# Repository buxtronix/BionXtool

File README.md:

# BionXtool

**BionXtool** is a tool for diagnostics, configuration, and real-time monitoring of BionX e-bike
components (Console, Battery, and Motor). Together with a cheap ($10) USB-CAN interface,
it can replace almost all of the functionality of the official BBI Software and hardware
interface ($100).

It is a fork of the original [BigXionFlasher](https://bigxionflasher.org) project,
with the following enhancements:

- Uses a cheap off the shelf USB Canbus adapter and standard Linux CAN networking
- Read and write any bike registers
- Real-time sniffing of the CANbus for diagnostics and more
- Sniff from PCAP files for offline analysis

I write this fork as I had dusted off my old mothballed BionX system, and needed to adjust some
limits to comply with updated legislation in my jurisdiction. With the company defunct, I couldn't
get a dealer to reset it, and wanted to use a cheap Aliexpress CAN adapter.

> [!WARNING]
> A non-compliant system must not be ridden in public spaces, any limits changed with this tool
> must be compliant with local regulations. As well as legal trouble, raising speed limits can
> put yourself, others, and your bike in danger.

> [!WARNING]
> Setting certain registers may leave your system unusable or difficult to recover. Please take
> extra care when manually setting registers.

---

## 🚀 Key Features

- **System Diagnostics**: View detailed hardware/software versions, serial numbers, and health statistics (cycle counts, temperature, voltage).
- **Configuration**: Modify speed limits (Assist, Throttle, and Min Speed), console preferences, accessory voltage and more
- **Advanced Sniffing**: Real-time or file-based (PCAP) CAN-bus monitoring with automatic register decoding into human-readable names and values.
- **Direct Register Access**: Read and write any specific BionX register from any node using hex IDs or friendly names.

For a detailed description of the BionX CANBus protocol, see [PROTOCOL.md](PROTOCOL.md)..

---

## 🛠 Installation

### Hardware prerequisites
- A BionX e-bike system using the CANBus protocol (post 2009 with G1/G2 console)
- A USB CANBus interface running Candlelight (e.g CANable 2.0)
- A way to physically connect to the bike CANBus (see below).

### Software Prerequisites
- A Linux system with **SocketCAN** support.
- `gcc` and `make` build tools.
- `libncurses` for monitor mode.

### Building from Source
```bash
git clone https://github.com/buxtronix/BionXtool.git
cd BionXtool
make
```

---

## 🔌 Hardware Setup

There are a few ways to interface with the CANBus on the bike. For reference,
see this [wiring diagram](images/pinout.png).

### Connect to the existing plugs

The official way to connect (which is what the dealer interface does) is to
use a tap cable inline where the console connector plug is. To do this, you
need a pair of Hirose connectors (HR30-6J-6P and HR30-6P-6S), wire all 6 pins
up in a straight through configuration, and tap off the GND, CAN_L and CAN_H
connections into the CANBus adapter.

The connectors are however fairly expensive (about $20/pair).

### Tap off the battery connector.

The cheapest way is to tap lines off the battery connector by just soldering
wires to them.

To access this, you need to remove the battery bracket off the bike, unscrew
the two Torx screws underneath, remove the metal bracket and you will get
access to the back of the plug. You may need to remove some hot glue first.
Then you just solder wires to tap off pins 2 (CAN_H), 5 (CAN_L) and GND. You
need to take care not to short or unsolder the wrong wires as there are
high currents and moderate voltages (50v) present.

### Console shim

I have developed a slim flex PCB that slides under the console where
it taps off the pogo pins. This is quite cheap, about $5 delivered from
JLCPCB, then once mounted you solder wires to the flex PCB that sticks out
from under the console.

For details, see [here](adapter-pcb/).

## 🔌 Software Setup

Most CANable adapters come from the factory with _slcan_ firmware, so you
will need to flash the _candlelight_ firmware onto it instead. This is really
simple, you just plug it into a computer and click a couple of buttons on
the [updater page](https://canable.io/updater/canable2.html).

BionX systems communicate at a bitrate of **125,000 bits/s**. Before running the
tool, you must bring up your CAN interface with the correct settings.

```bash
# Bring up can0 with the BionX bitrate (125k)
sudo ip link set can0 type can bitrate 125000
sudo ip link set can0 up
```

If you are testing without hardware, you can use a virtual CAN interface:
```bash
sudo modprobe vcan
sudo ip link add dev vcan0 type vcan
sudo ip link set vcan0 up
./BionXtool -d vcan0 -S
```
---

## 📖 Usage

BionXtool provides several modes of operation, from high-level configuration to low-level protocol analysis.

### 1. System Overview & Diagnostics
Retrieve a comprehensive report of all connected components, including software versions, battery health, and odometer.

```bash
# Print all system settings and statistics
$ ./BionXtool -s
BionXtool V 0.1 (BionXtool)
 (c) 2026 by Ben Buxton <bbuxton@gmail.com>

console already in slave mode. good!

Console information:
 hardware version ........: 0x15
 software version ........: 0x64
 manufacture date ........: 13/01/2014
 assistance level ........: 3 (0x03)
 part number .............: 03205
 item number .............: 00342
 max limit enabled .......: yes
 speed limit .............: 26.0 km/h
 min limit enabled .......: yes
 min speed limit .........: 0.2 km/h
 throttle limit enabled ..: yes
 throttle speed limit ....: 6.0 km/h
 wheel circumference .....: 2075
 mountain cap ............: 54.69%
 odo .....................: 14258.40 km

Battery information:
 hardware version ........: 0x63
 software version ........: 0x112
 manufacture date ........: 07/09/2017
 part number .............: 05560
 item number .............: 00342
 voltage .................: 53.13 V
 battery level ...........: 100.00%
 maximum voltage .........: 112.08%
 minimum voltage .........: 95.42%
 mean voltage ............: 110.00%
 resets ..................: 0
 lmd .....................: 10.40 Ah
 cell capacity ...........: 2.15 Ah
 charge time worst .......: 113
 charge time mean ........: 0
 charge cycles ...........: 268
 full charge cycles ......: 0
 power cycles ............: 969
 battery temp max ........: 80°C
 battery temp min ........: -17°C
 accessory voltage config.: 8.20 V
 RTC timestamp............: 2088d 16:40:16

 charge level @ 010% : 0015
 charge level @ 020% : 0015
 charge level @ 030% : 0072
 charge level @ 040% : 0088
 charge level @ 050% : 0023
 charge level @ 060% : 0028
 charge level @ 070% : 0020
 charge level @ 080% : 0004
 charge level @ 090% : 0003
 charge level @ 100% : 0003
 total # of charges .: 0271

 balancer enabled ...: no

 voltage cell #01 ...: 4.085V
 voltage cell #02 ...: 4.083V
 voltage cell #03 ...: 4.080V
 voltage cell #04 ...: 4.086V
 voltage cell #05 ...: 4.081V
 voltage cell #06 ...: 4.088V
 voltage cell #07 ...: 4.086V
 voltage cell #08 ...: 4.091V
 voltage cell #09 ...: 4.098V
 voltage cell #10 ...: 4.083V
 voltage cell #11 ...: 4.066V
 voltage cell #12 ...: 4.114V
 voltage cell #13 ...: 4.088V
 temperature pack #01: 29°C
 temperature pack #02: 29°C
 temperature pack #03: 29°C
 temperature pack #04: 29°C
 temperature pack #05: 14°C

Motor information:
 hardware version ........: 0x32
 software version ........: 0x102
 manufacture date ........: 09/11/2017
 temperature .............: 37°C
 speed limit .............: 26 km/h
 wheel circumference .....: 2075
 part number .............: 05989
 item number .............: 00342

```

### 2. Configuring System Limits & Geometry
Adjust the behavior of the bike to match local regulations or your preferences.

```bash
# Set assist speed limit to 32.0 km/h (0 for unlimited)
./BionXtool -l 32.0

# Set throttle speed limit to 20.0 km/h
./BionXtool -t 20.0

# Set minimum assist speed (speed at which motor kicks in)
./BionXtool -m 2.0

# Update wheel circumference (in mm) for accurate speed/distance
./BionXtool -c 2073

# Set initial assist level on power-up (0-4)
./BionXtool -a 2

# Set mountain cap level (assist percentage)
./BionXtool -o 55

# Set clock to current local time
./BionXtool -T
```

### 3. Battery & Accessory Configuration
Configure battery-specific settings like accessory port voltage.

```bash
# Set accessory port voltage (6.0V to 14.0V)
./BionXtool -v 12.0

# Enable/Disable accessory power (1=On, 0=Off)
./BionXtool -A 1
```

### 4. CAN Bus Monitoring & Sniffing
Analyze the live communication between the console, battery, and motor.

```bash
# Real-time TUI dashboard (Top-like interface)
./BionXtool -M

# Stream every CAN packet with human-readable decoding
./BionXtool -S

# Stream only when a register value changes
./BionXtool -C

# Analyze a previously captured PCAP file
./BionXtool -f capture.pcap
```

Included in this repo are two captures. `bike-on-off.pcap` is a raw PCAP sniff
from my bike being turned on, then turned off shortly after. `bike-on-off-txt`
is the same but decoded.

### 5. Direct Register Access (Expert)
Read or write individual registers on any node. Useful for advanced features or deep troubleshooting.

```bash
# Read Battery Hardware Revision (0x3B)
./BionXtool -R battery 0x3B

# Set config to enable accessory power at bike turn-on.
./BionXtool -W console 0x80 0x1
```

An almost complete list of all registers is in [registers.h](registers.h). Note
that interacting with the console requires first setting it into slave mode (-z),
however this is not required for other components.

### 6. Power & State Control
Force system states or perform remote operations.

```bash
# Power off the entire system
./BionXtool -p

# Force console into slave mode (for external control)
./BionXtool -z

# Run commands without attempting to trigger slave mode
./BionXtool -n -S
```

---

## 📋 Command Line Options

| Option | Argument | Description |
| :--- | :--- | :--- |
| **Global** | | |
| `-d` | `<device>` | CAN device interface (default: `can0`) |
| `-h` | | Print help screen |
| **Information** | | |
| `-s` | | Print system settings overview |
| `-i` | | Hide private serial and part numbers |
| **Configuration** | | |
| `-l` | `<speed>` | Set assist speed limit (0-70 km/h, 0=unlimited) |
| `-t` | `<speed>` | Set throttle speed limit (0-70 km/h) |
| `-m` | `<speed>` | Set minimum assist speed (0-30 km/h) |
| `-c` | `<mm>` | Set wheel circumference (in mm) |
| `-a` | `<level>` | Set initial assist level (0-4) |
| `-o` | `<pct>` | Set mountain cap assist level (0-100%) |
| `-v` | `<volt>` | Set battery accessory voltage (6.0 - 14.0V) |
| `-A` | `<0\|1>` | Set battery accessory power (0=off, 1=on) |
| `-T` | | Update clock (RTC). Stored in battery |
| **Sniffing** | | |
| `-M` | | **Monitor Mode**: Interactive TUI dashboard |
| `-S` | | **Sniff Mode**: Stream decoded packets |
| `-C` | | **Change Sniff**: Stream only changed values |
| `-f` | `<file>` | Sniff from a PCAP file |
| **Low-level** | | |
| `-R` | `<node> <reg>`| Read specific register (hex) from node (name or hex) |
| `-W` | `<node> <reg> <val>`| Write value to specific register |
| `-z` | | Force console into slave mode |
| `-n` | | Do NOT attempt to trigger slave mode |
| `-p` | | Power off system |

---

## 🛠Changelog

- 2026-04-14: rtc support. various register clarifications
- 2026-03-28: added adapter pcb info
- 2026-03-06: initial version

## ⚖️ License & Attribution

**BionXtool** is licensed under the **GPLv3**.

This project is a fork of **BigXionFlasher**, originally developed by **Thomas König**. 
It includes software developed by the BigXionFlasher Project (http://www.bigxionflasher.org/).

Gemini CLI is used to assist coding tasks. Actual hardware engineering lovingly
done by hand :)

**Author of this fork:** Ben Buxton <bbuxton@gmail.com> (2026)

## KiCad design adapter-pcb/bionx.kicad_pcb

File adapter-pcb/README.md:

# Bionx Console Adapter

This contains Kicad designs for a flex PCB that can be slotted under the
G2 console for easy interfacing with the bike's CAN bus.

The PCB breaks out all of the pins from the console (including throttle).

## Manufacture

The file `gerbers.zip` contains all of the necessary fab files and it
can be uploaded directly to JLCPCB and other board houses, with no
further changes necessary.

JLCPCB currently has a deal where you can get 5 x flex PCBs for $2,
and if you use their lowest cost shipping option, you can get these
delivered for a total of around $5-6.

Five easy steps to order:

1. Go to [JLCPCB](https://jlcpcb.com/)
2. Click on the *Get Instant Quote* button (no need to change the options next to it).
3. Click *Add gerber file* and upload the _gerbers.zip_ file from here.
4. Select *Flex* as the base material. You will see a yellow render of the PCB.
5. Change no other options, just click *Save to cart* and finalise the order.

If you select *Global Standard Direct Line* shipping, this will cost a
little over $3, rather than $20+ for DHL/Fedex, though will take a couple
of weeks.

The $2 deal is for 0.11mm PCB - thicker options are much more expensive,
but this one works (you may want to manually add a stiffening film).

## Usage

The PCB simply slips into the console holder, ensuring the PCB pads line
up with the metal pads, then slide the console on, taking care not to
let the PCB slip.

On mine, I added a little extra rigidity by using some 0.2mm mylar
sheet that I cut and added holes for the PCB pads, using contact cement
to bond them together. You don't have to do this, but you need to
be a little careful at preventing the PCB from slipping.

You can then solder wires to the GND, CAN_L and CAN_H pads, which you
then connect to your CANBus adapter. I used soft silicone wire and hot
glue - more rigid wire and/or no hot glue risks tearing the pads off.

The other pins are also broken out for those who want to experiment more.

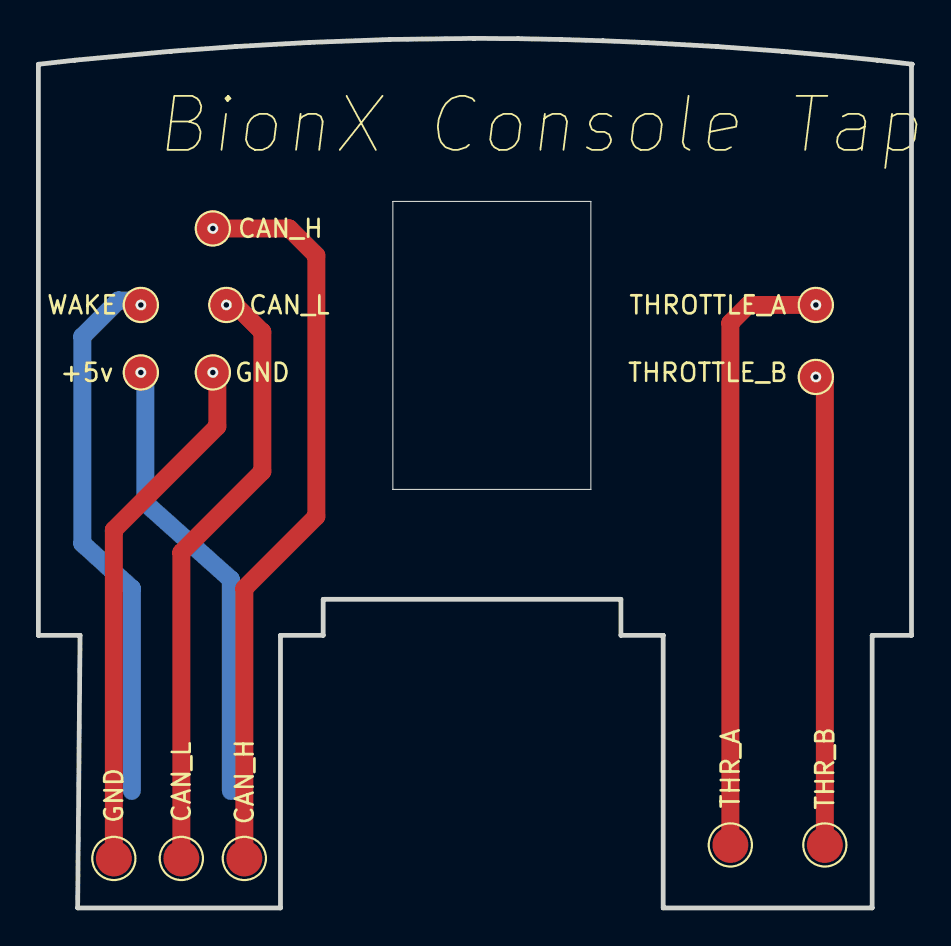
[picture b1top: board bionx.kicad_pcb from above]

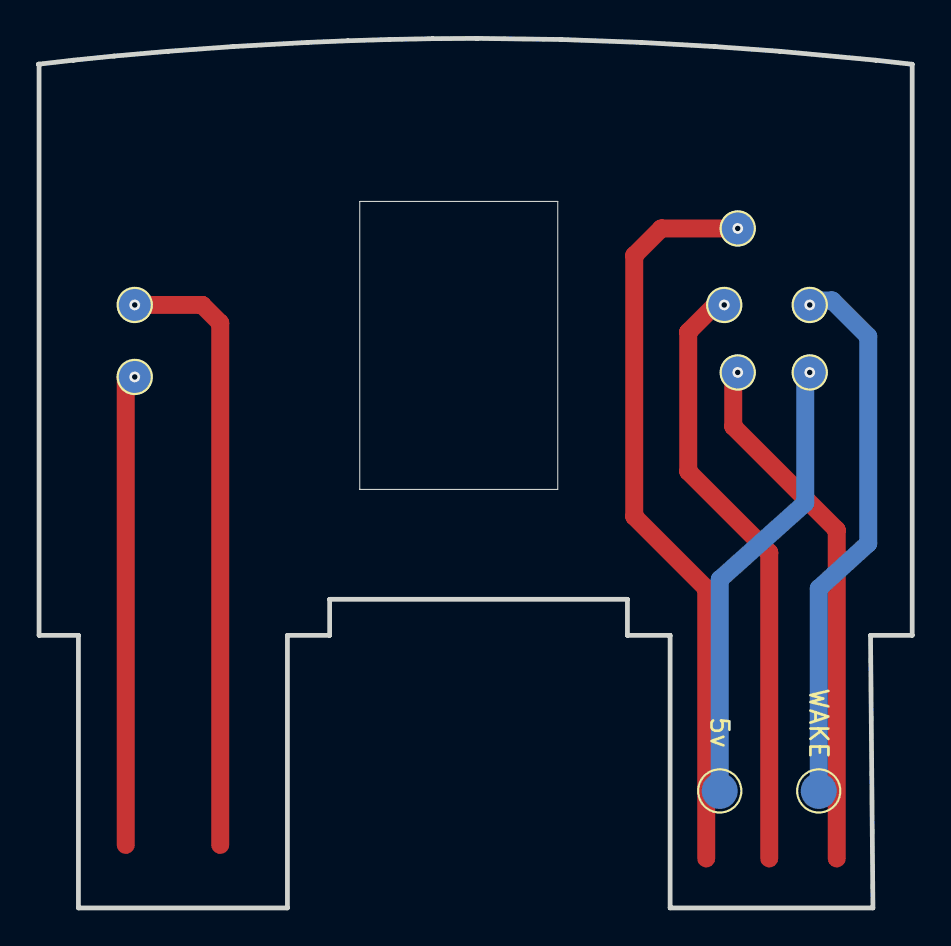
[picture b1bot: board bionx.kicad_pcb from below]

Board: 2 copper layers, 48.5 x 48.3 mm, 21 parts (9 on the bottom side), 7 nets.

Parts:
5v: TestPoint; TestPoint_Pad_D2.0mm
+5v: TestPoint; TestPoint_Pad_D1.5mm
CAN_H: TestPoint; TestPoint_Pad_D1.5mm
CAN_H#2: TestPoint; TestPoint_Pad_D2.0mm
CAN_L: TestPoint; TestPoint_Pad_D1.5mm
CAN_L#2: TestPoint; TestPoint_Pad_D2.0mm
GND: TestPoint; TestPoint_Pad_D2.0mm
GND#2: TestPoint; TestPoint_Pad_D1.5mm
THROTTLE_A: TestPoint; TestPoint_Pad_D1.5mm
THROTTLE_B: TestPoint; TestPoint_Pad_D1.5mm
THR_A: TestPoint; TestPoint_Pad_D2.0mm
THR_B: TestPoint; TestPoint_Pad_D2.0mm
TP1, TP11, TP13, TP16, TP17, TP18, TP19: TestPoint; TestPoint_Pad_D1.5mm
WAKE: TestPoint; TestPoint_Pad_D1.5mm
WAKE#2: TestPoint; TestPoint_Pad_D2.0mm

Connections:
/5v: 5v.1, +5v.1, TP1.1
/CAN_H: CAN_H.1, CAN_H#2.1, TP17.1
/CAN_L: CAN_L.1, CAN_L#2.1, TP18.1
/GND: GND.1, GND#2.1, TP16.1
/THR_1: THROTTLE_A.1, THR_A.1, TP11.1
/THR_2: THROTTLE_B.1, THR_B.1, TP13.1
/WAKE: TP19.1, WAKE.1, WAKE#2.1

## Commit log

2026-03-05 Documentation updates
2026-03-06 documentation tweaks
2026-03-07 doc updates
2026-03-07 markdown fix
2026-03-28 Sniffing age-out, plus add adapter PCB
2026-03-28 Fixes image link typo
2026-03-28 Fixes image link
2026-04-13 rtc support, register clarifications
